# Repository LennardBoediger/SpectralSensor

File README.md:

# Spectral Measurement Platform
Das hier ist ein clone der Benutzer software

Vollständiges Repository: (https://github.com/LennardBoediger/SpectralSensor)
bachelorarbeit.pdf
Platinen Layout
Latex files

### Usage

Flash the SD image
 Attach 1-20 Sensorboards in sereries
 Connect to the Pi over SSH
 start a detachable screen 
 make compiles and runs the software

 ssh pi@[IP-ADRESSE]
 git clone https://github.com/LennardBoediger/SpectralSensor
 cd SpectralSensor 
 screen
 make

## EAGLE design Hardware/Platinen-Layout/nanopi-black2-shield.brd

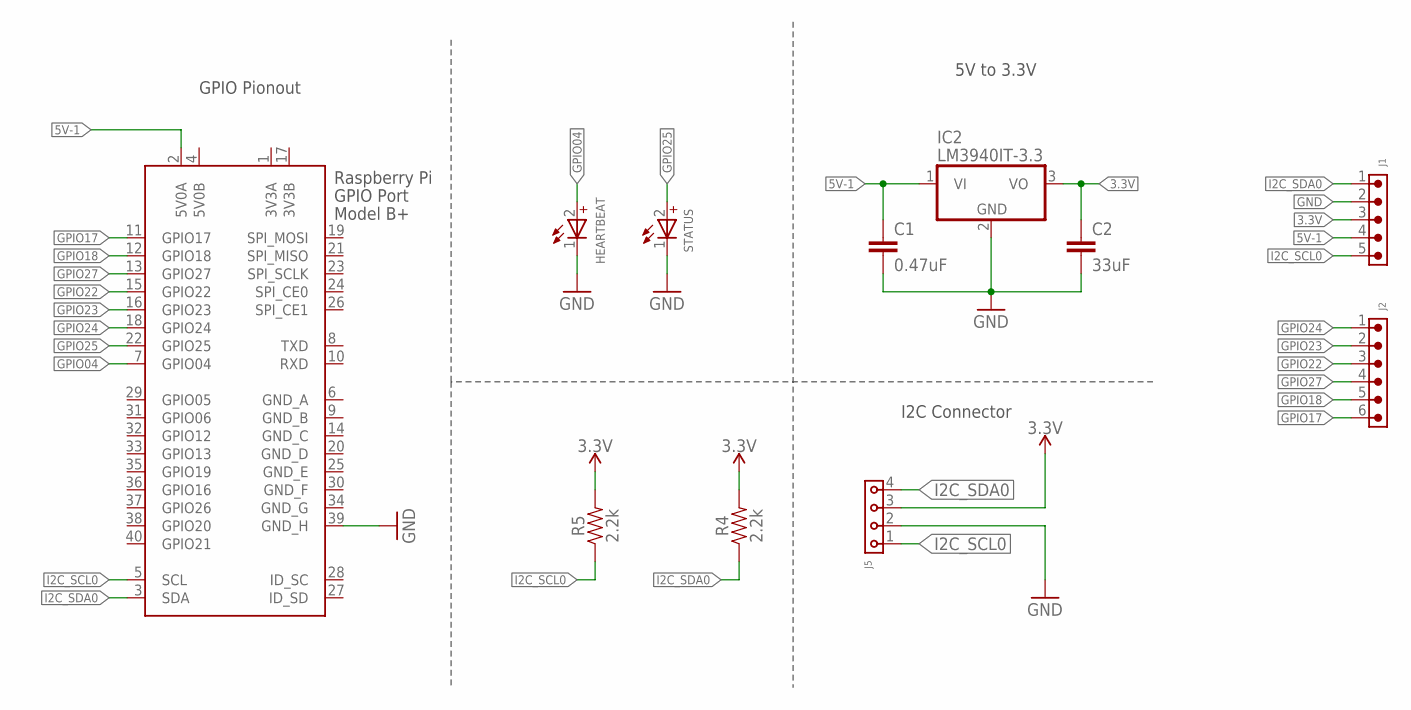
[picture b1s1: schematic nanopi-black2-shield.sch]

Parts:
C1: 0.47uF; 0603
C2: 33uF; C0805
HEARTBEAT: WL-SMSW_0603_REC_155060RS75300; WL-SMSW_0603_REC
IC2: LM3940IT-3.3; TO220H
J1: 6130XX11121_61300511121; 61300511121
J2: 6130XX11121_61300611121; 61300611121
J5: 6130XX11821_61300411821; 61300411821
R4, R5: 2.2k; 0603
STATUS: WL-SMSW_0603_REC_155060GS75300; WL-SMSW_0603_REC
X1: RASPI_BOARD_B+#_HDC; RASPI_BOARD_B+HAT_DF_CF

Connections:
3.3V: C2.1, IC2.3 (VO), J1.3, J5.3, R4.2, R5.2
3V3A: X1.1 (3V3A)
3V3B: X1.17 (3V3B)
5V0B: X1.4 (5V0B)
5V-1: C1.1, IC2.1 (VI), J1.4, X1.2 (5V0A)
GND: C1.2, C2.2, HEARTBEAT.1 (-), IC2.2 (GND), J1.2, J5.2, STATUS.1 (-), X1.39 (GND_H)
GND_A: X1.6 (GND_A)
GND_B: X1.9 (GND_B)
GND_C: X1.14 (GND_C)
GND_D: X1.20 (GND_D)
GND_E: X1.25 (GND_E)
GND_F: X1.30 (GND_F)
GND_G: X1.34 (GND_G)
GPIO04: HEARTBEAT.2 (+), X1.7 (GPIO04)
GPIO17: J2.6, X1.11 (GPIO17)
GPIO18: J2.5, X1.12 (GPIO18)
GPIO22: J2.3, X1.15 (GPIO22)
GPIO23: J2.2, X1.16 (GPIO23)
GPIO24: J2.1, X1.18 (GPIO24)
GPIO25: STATUS.2 (+), X1.22 (GPIO25)
GPIO27: J2.4, X1.13 (GPIO27)
I2C_SCL0: J1.5, J5.1, R5.1, X1.5 (SCL)
I2C_SDA0: J1.1, J5.4, R4.1, X1.3 (SDA)

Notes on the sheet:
I2C Connector
5V to 3.3V
GPIO Pionout

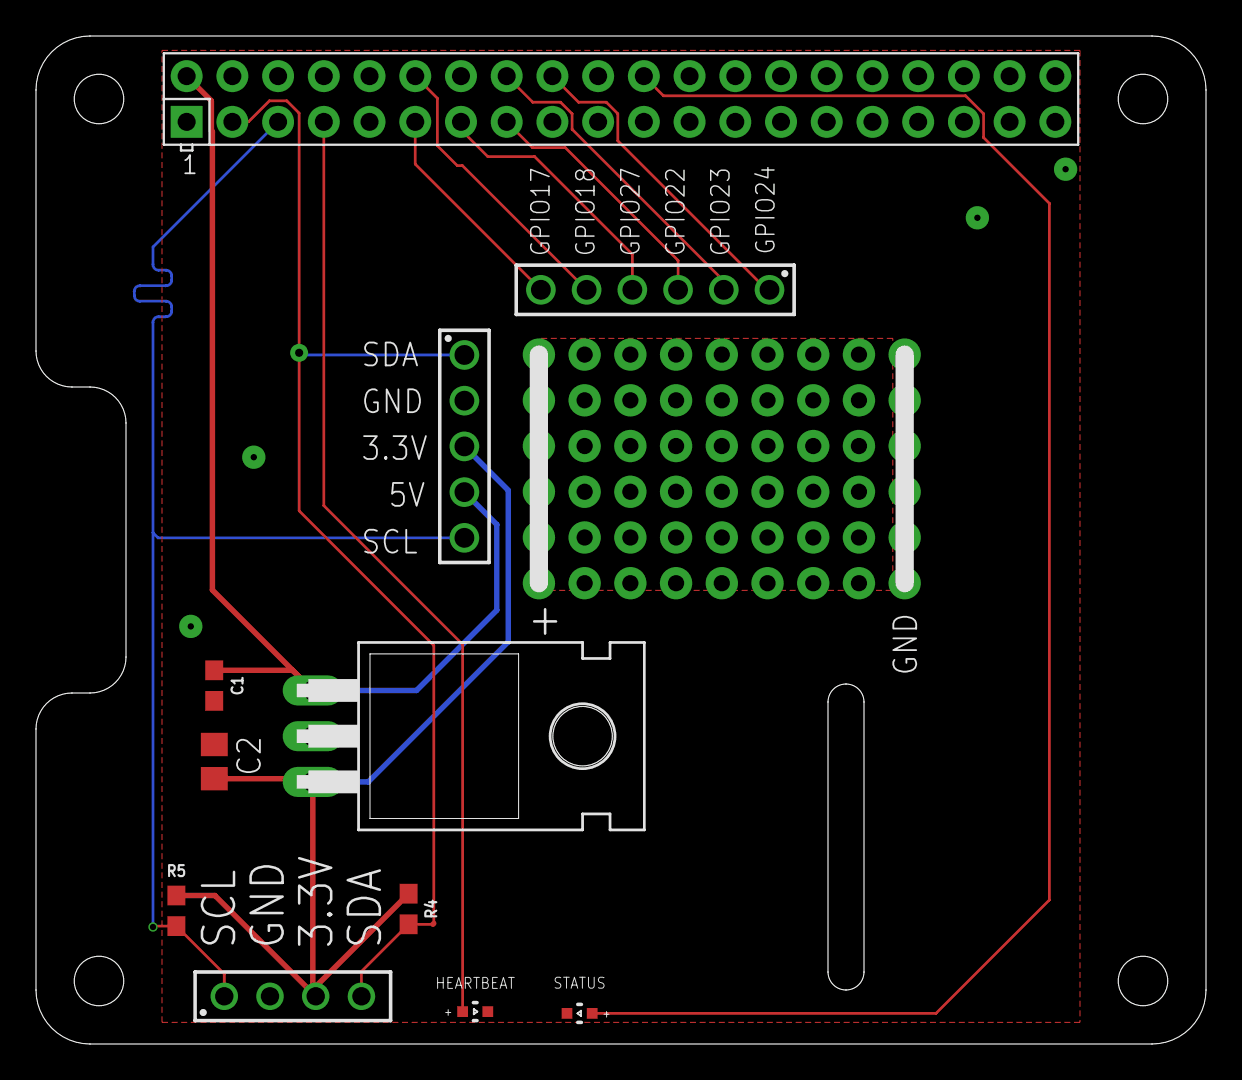
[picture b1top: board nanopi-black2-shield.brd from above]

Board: 2 copper layers, 65.0 x 56.0 mm, 11 parts (0 on the bottom side), 13 nets.

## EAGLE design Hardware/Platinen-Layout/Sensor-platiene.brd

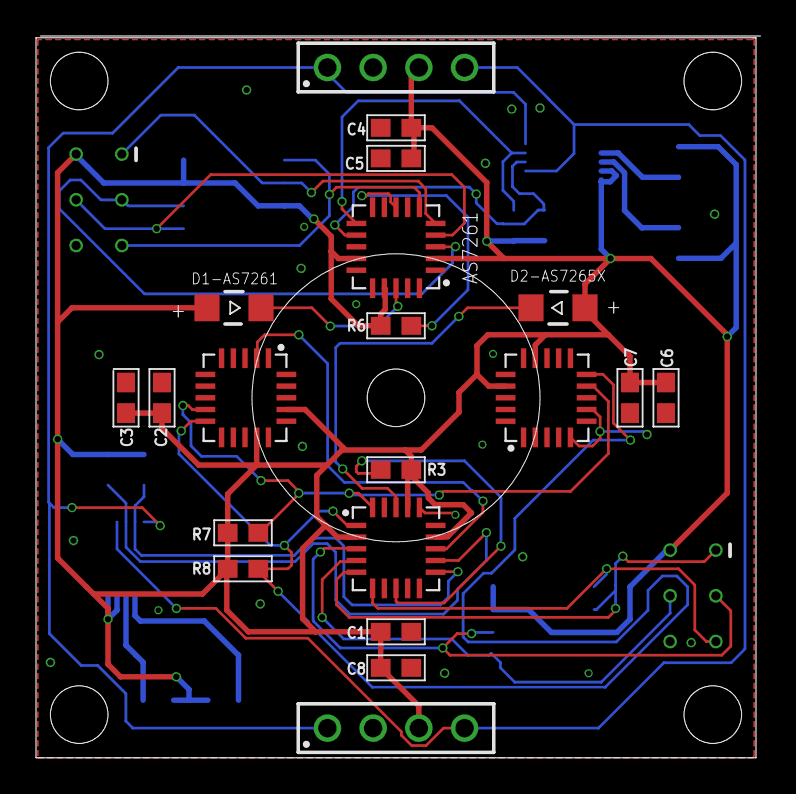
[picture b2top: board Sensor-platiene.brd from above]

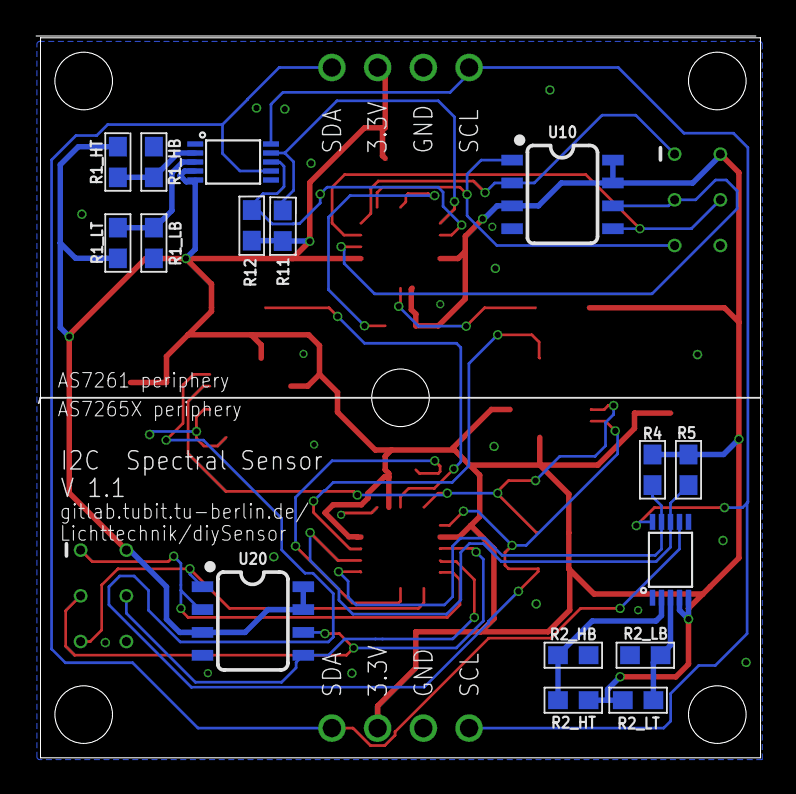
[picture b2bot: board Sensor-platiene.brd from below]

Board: 2 copper layers, 40.2 x 40.1 mm, 43 parts (18 on the bottom side), 27 nets.

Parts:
AS7261: IR; LGA20
C1, C2, C5, C7: 10uF; 0603
C3, C4, C6, C8: 100nF; 0603
D1-AS7261, D2-AS7265X: WL-SMCW_1206
J1, J3: 61300411821
J5, J10: Flash Programming; 2X3_TEST_POINTS
R1_HB, R1_HT, R1_LB, R1_LT, R2_HB, R2_HT, R2_LB, R2_LT, R4, R5, R7, R8, R11, R12: 2.2k; 0603
R3, R6: 10k; 0603
U1: AS72651; LGA20
U5: AS72653; LGA20
U6: AS72652; LGA20
U10, U20: AT25SF041; SO08
U$1, U$2: LTC4316; MS-PACKAGE
U$3, U$4, U$5, U$6, U$7: 3-2MM-HOLE

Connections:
3.3V: AS7261.2, AS7261.14, AS7261.17, C1.1, C2.1, C3.1, C4.1, C5.1, C6.1, C7.1, C8.1, D1-AS7261.2, D2-AS7265X.2, J1.3, J3.3, J5.2, J10.2, R1_HT.2, R1_LT.2, R2_HT.2, R2_LT.2, R3.2, R4.2, R5.2, R6.2, R7.2, R8.2, R11.2, R12.2, U1.2, U1.14, U1.17, U5.14, U5.17, U6.14, U6.17, U10.3, U10.7, U10.8, U20.3, U20.7, U20.8, U$1.4, U$1.5, U$2.4, U$2.5
!CS_EE: J5.5, U1.6, U20.1
!CS_EE2: AS7261.6, J10.5, U10.1
!RST-ADDR: U1.13, U6.2
GND: AS7261.16, C1.2, C2.2, C3.2, C4.2, C5.2, C6.2, C7.2, C8.2, J1.2, J3.2, J5.6, J10.6, R1_HB.1, R1_LB.1, R2_HB.1, R2_LB.1, U1.16, U5.5, U5.7, U5.16, U6.5, U6.7, U6.16, U10.4, U20.4, U$1.1, U$2.1
I2C_ENB: R3.1, U1.8
MISO: J5.1, U1.5, U20.2
MISO2: AS7261.5, J10.1, U10.2
MOSI: J5.4, U1.4, U20.5
MOSI2: AS7261.4, J10.4, U10.5
unnamed: AS7261.18, D1-AS7261.1
unnamed: D2-AS7265X.1, U1.18
unnamed: AS7261.8, R6.1
SCK: J5.3, U1.3, U20.6
SCK2: AS7261.3, J10.3, U10.6
SCL-PI: J1.1, J3.1, U$1.10, U$2.10
SCL-SENSOR-1: AS7261.11, R11.1, U$2.9
SCL-SENSOR-2: R4.1, U1.11, U$1.9
SCL_S: R7.1, U1.20, U5.9, U6.9
SDA-PI: J1.4, J3.4, U$1.7, U$2.7
SDA-SENSOR-1: AS7261.12, R12.1, U$2.8
SDA-SENSOR-2: R5.1, U1.12, U$1.8
SDA_S: R8.1, U1.1, U5.10, U6.10
XORH-1: R1_HB.2, R1_HT.1, U$2.2
XORH-2: R2_HB.2, R2_HT.1, U$1.2
XORL-1: R1_LB.2, R1_LT.1, U$2.3
XORL-2: R2_LB.2, R2_LT.1, U$1.3

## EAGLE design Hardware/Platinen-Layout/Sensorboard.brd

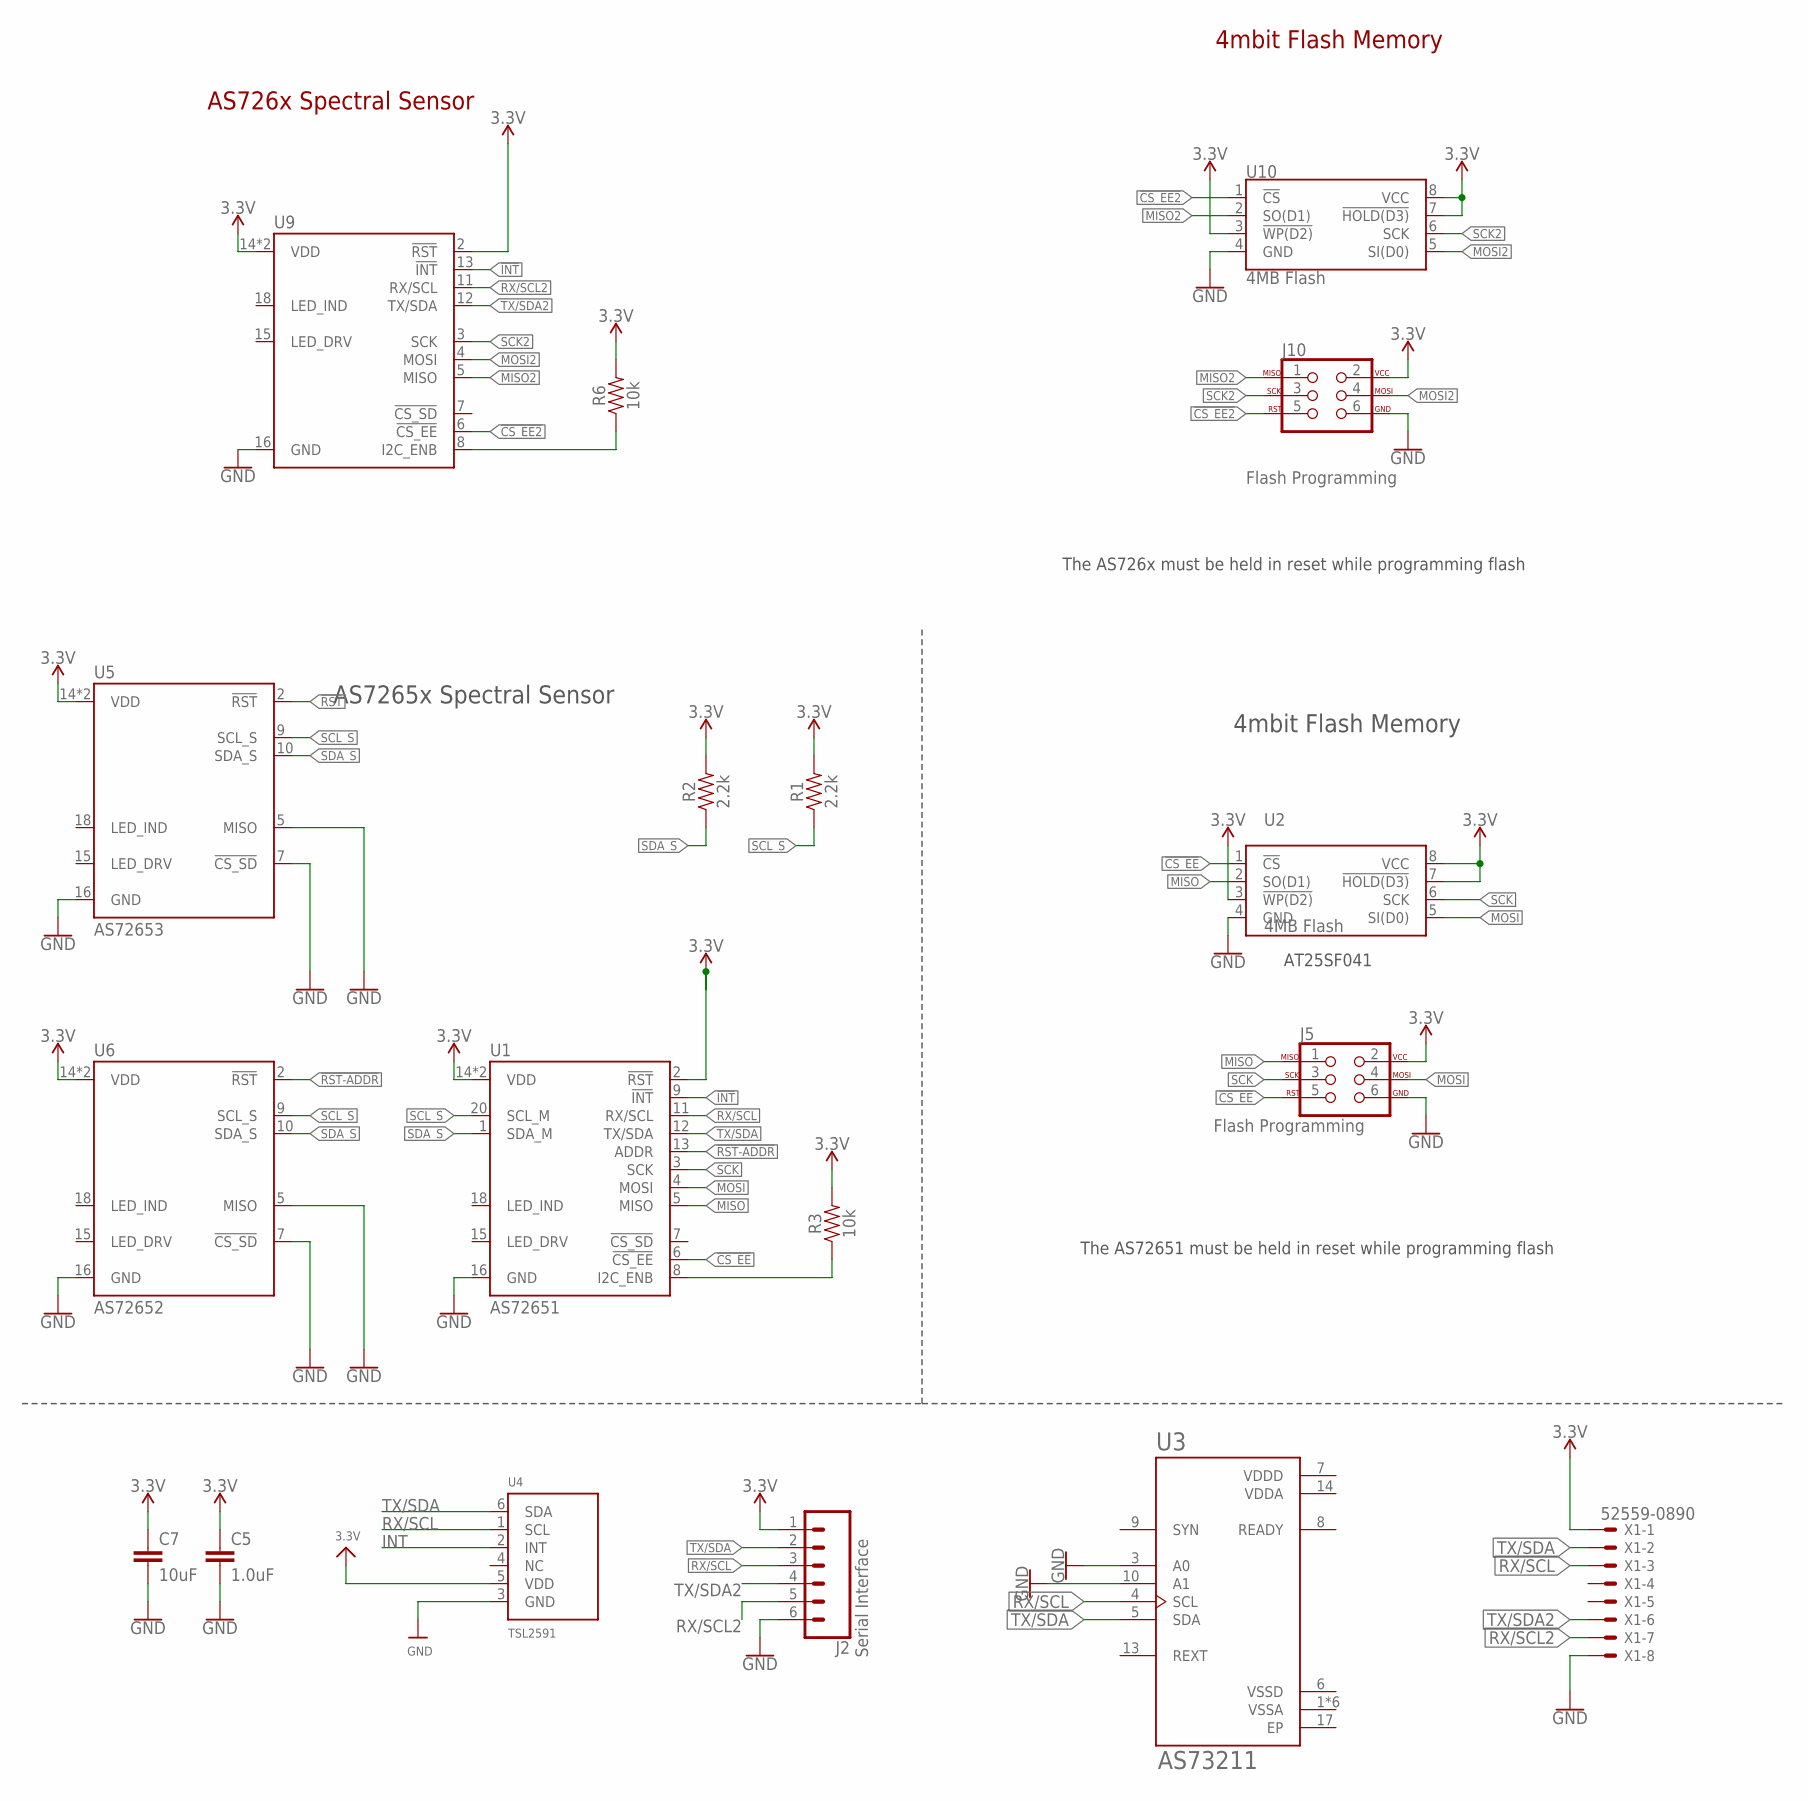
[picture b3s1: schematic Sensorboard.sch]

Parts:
C5: 1.0uF; 0603
C7: 10uF; 0603
J2: Serial Interface; 1X06_NO_SILK
J5, J10: Flash Programming; 2X3_TEST_POINTS
R1, R2: 2.2k; 0603
R3, R6: 10k; 0603
U1: AS72651; LGA20
U2, U10: 4MB Flash; SO08
U3: AS73211; QFN65P400X400X100-17N
U4: TSL2591; DFN6_TAOS
U5: AS72653; LGA20
U6: AS72652; LGA20
U9: IR; LGA20
X1: 52559-0890

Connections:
3.3V: C5.1, C7.1, J2.1, J5.2, J10.2, R1.2, R2.2, R3.2, R6.2, U1.2 (!RST), U1.14 (VDD), U1.17 (VDD), U2.3 (!WP(D2)), U2.7 (!HOLD(D3)), U2.8 (VCC), U4.5 (VDD), U5.14 (VDD), U5.17 (VDD), U6.14 (VDD), U6.17 (VDD), U9.2 (!RST), U9.14 (VDD), U9.17 (VDD), U10.3 (!WP(D2)), U10.7 (!HOLD(D3)), U10.8 (VCC), X1.1
!CS_EE: J5.5, U1.6 (!CS_EE), U2.1 (!CS)
!CS_EE2: J10.5, U9.6 (!CS_EE), U10.1 (!CS)
!INT: U1.9 (!INT), U9.13 (!INT)
!RST: U5.2 (!RST)
!RST-ADDR: U1.13 (ADDR), U6.2 (!RST)
EP: U3.17 (EP)
GND: C5.2, C7.2, J2.6, J5.6, J10.6, U1.16 (GND), U2.4 (GND), U3.3 (A0), U3.10 (A1), U4.3 (GND), U5.5 (MISO), U5.7 (!CS_SD), U5.16 (GND), U6.5 (MISO), U6.7 (!CS_SD), U6.16 (GND), U9.16 (GND), U10.4 (GND), X1.8
I2C_ENB: R3.1, U1.8 (I2C_ENB)
INT: U4.2 (INT)
MISO: J5.1, U1.5 (MISO), U2.2 (SO(D1))
MISO2: J10.1, U9.5 (MISO), U10.2 (SO(D1))
MOSI: J5.4, U1.4 (MOSI), U2.5 (SI(D0))
MOSI2: J10.4, U9.4 (MOSI), U10.5 (SI(D0))
unnamed: R6.1, U9.8 (I2C_ENB)
RX/SCL: J2.3, U1.11 (RX/SCL), U3.4 (SCL), U4.1 (SCL), X1.3
RX/SCL2: J2.5, U9.11 (RX/SCL), X1.7
SCK: J5.3, U1.3 (SCK), U2.6 (SCK)
SCK2: J10.3, U9.3 (SCK), U10.6 (SCK)
SCL_S: R1.1, U1.20 (SCL_M), U5.9 (SCL_S), U6.9 (SCL_S)
SDA_S: R2.1, U1.1 (SDA_M), U5.10 (SDA_S), U6.10 (SDA_S)
TX/SDA: J2.2, U1.12 (TX/SDA), U3.5 (SDA), U4.6 (SDA), X1.2
TX/SDA2: J2.4, U9.12 (TX/SDA), X1.6
VDDA: U3.14 (VDDA)
VDDD: U3.7 (VDDD)
VSSA: U3.1 (VSSA), U3.2 (VSSA), U3.11 (VSSA), U3.12 (VSSA), U3.15 (VSSA), U3.16 (VSSA)
VSSD: U3.6 (VSSD)

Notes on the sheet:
AS7265x Spectral Sensor
4mbit Flash Memory
The AS72651 must be held in reset while programming flash
AT25SF041
AS726x Spectral Sensor
The AS726x must be held in reset while programming flash

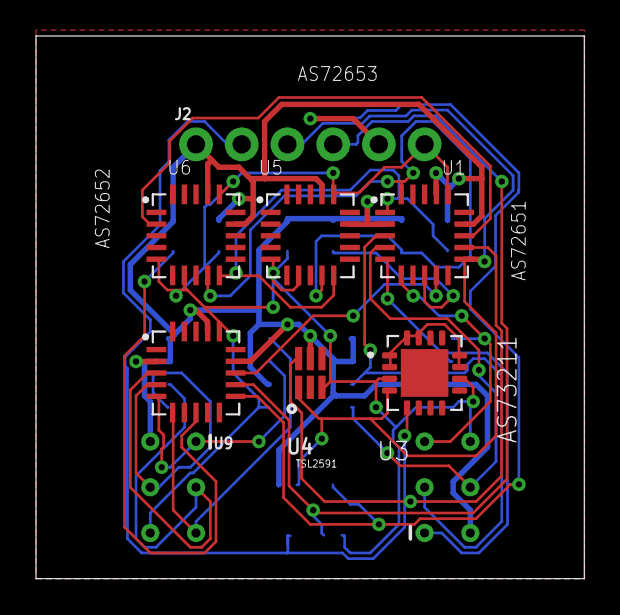
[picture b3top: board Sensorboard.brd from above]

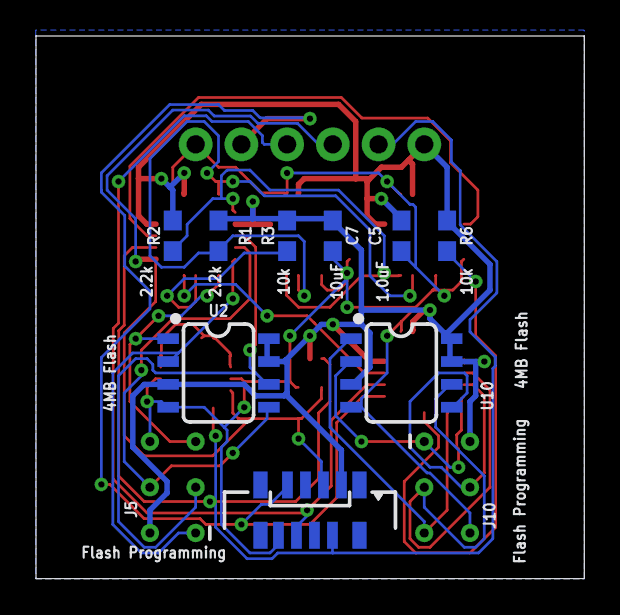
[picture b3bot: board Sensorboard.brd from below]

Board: 2 copper layers, 30.5 x 30.2 mm, 18 parts (11 on the bottom side), 21 nets.

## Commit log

2020-05-06 Add notizen
2020-05-06 gitignore
2020-05-11 notes for complete GI setup
2020-05-11 c code makefile
2020-05-27 working virtual Read
2020-05-27 new lib folder starting to port led working =)
2020-05-27 portri porti port porrt
2020-05-27 portri porti port porrt 2
2020-05-27 porti ist fertig
2020-05-30 scematic is done
2020-05-30 basic hols in board
2020-05-30 board alingnment done
2020-05-30 board is a mess
2020-05-31 board is getting there
2020-05-31 board is better
2020-05-31 board is better2
2020-05-31 almost done
2020-05-31 almost done2
2020-05-31 todo ground plane
2020-05-31 todo ground plane next try
2020-05-31 board is done TODO: change hole size- shild scematic done
2020-06-22 latex template!!!
2020-06-22 add latex expose
2020-08-11 remove trash
2020-08-21 add write to db
2020-08-21 fixed write to db
2020-08-21 write to db works :)
2020-08-23 add new values to db
2020-09-05 new hardware version
2020-09-07 add heatsink to board
2020-09-13 new hardware + test code
2020-09-14 sensor detection + read all values + hardware check
2020-09-14 fancy output
2020-09-16 added setting
2020-09-18 latex Software chapter
2020-09-21 read everything
2020-09-21 reorganise structure
2020-09-21 release 1.0
2020-09-24 auto_gain
2020-09-26 new adapter Board
2020-09-26 relase 1.1 is comming
2020-09-26 lol delete csv again fuck my life
2020-09-26 Version 1.1 Relase - just added shitty features 1.0 is king
2020-10-11 1.1 release fixed time issue and has a new file structure
2020-10-20 Latex in the rain
2020-10-21 add register tables in latex
2020-11-12 add einleitung in latex
2020-12-26 latex tex tex
2021-01-05 add Readme.md
2021-01-05 Readme.md add img
2021-01-16 latex cleanup
2021-01-16 code cleanup
2021-01-18 code is clean
2021-01-18 add Manual Trigger Feature
2021-01-27 spellcheck latex
2021-01-29 latex todo list
2021-01-30 latex titlepage fix
2021-01-30 latex todo 2
2021-02-01 Latex Fertig
2021-02-05 clean Gain Plot
2021-02-05 add fancy comments to code
2021-02-07 12 boards working - mux Done
2021-02-20 fixes to influxdb-lib
2021-03-12 cean up abgabe files
2021-03-12 New easy to integrate 1.4 Release
2021-03-12 rm empty folder
2021-03-12 Update README.md
    fix images
2021-03-26 change link to repoin latex
2021-03-26 Update welcome.c
    change git repo links
2021-03-26 Update welcome.c
    remove https from git link
2021-03-26 new pdf
2021-03-26 fix usage in readme
2021-03-26 add stuff from gitW
    #
2021-03-26 Revert "add stuff from gitW"
    This reverts commit b289d961393d5d6742d5daff51f6af8780659001.
2021-05-02 Update AS726X.c
    scan all mux channel!

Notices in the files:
parts and their libraries:
SparkFun-Capacitors: Licensing: Creative Commons ShareAlike 4.0 International - https://creativecommons.org/licenses/by-sa/4.0
150120RS75000_Eagle_WL-SMCW_rev20b: Copyright: Würth Elektronik
lm1117: (c) 2014 Samuel Lourenço
